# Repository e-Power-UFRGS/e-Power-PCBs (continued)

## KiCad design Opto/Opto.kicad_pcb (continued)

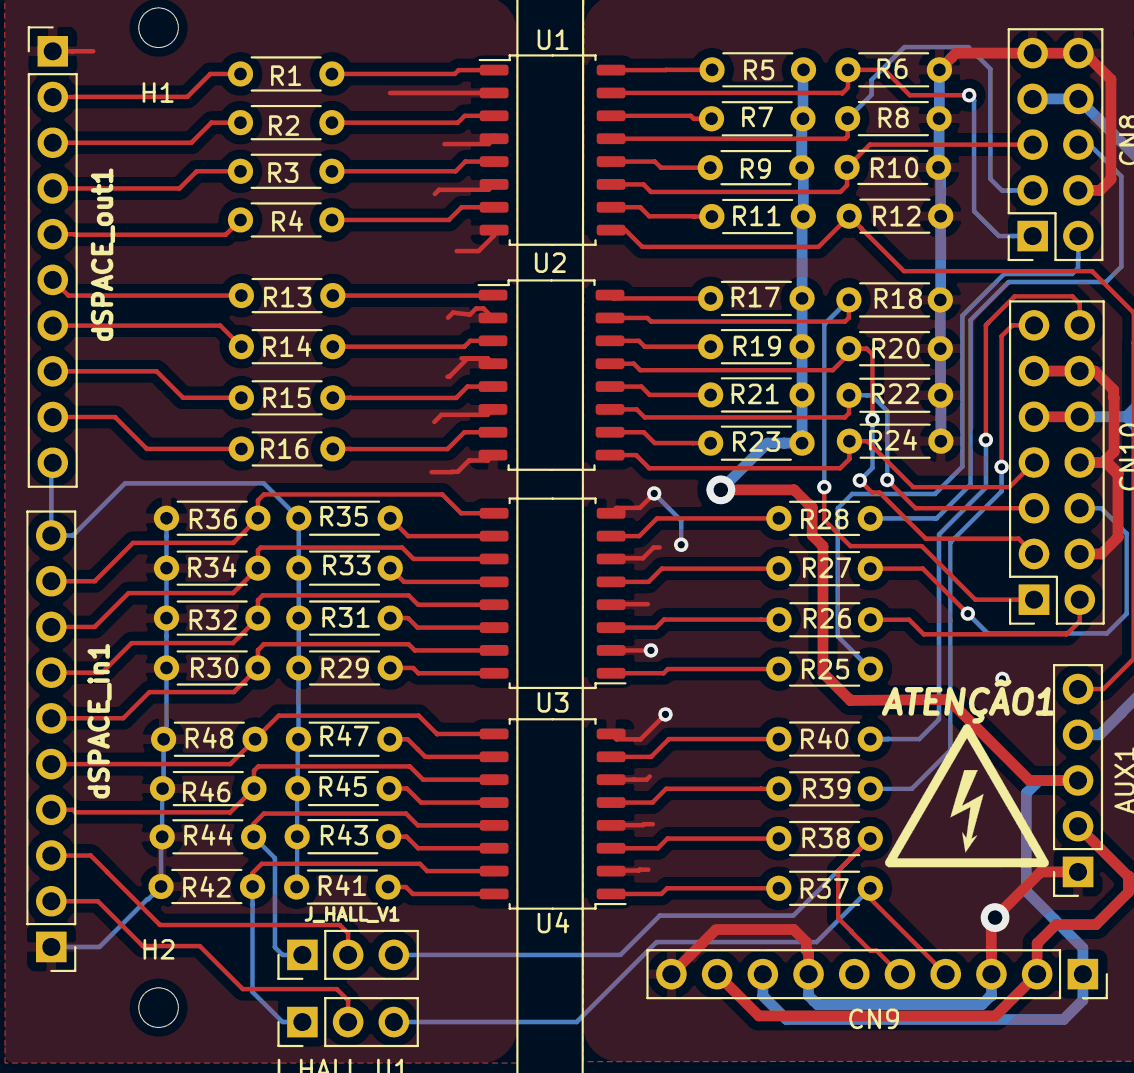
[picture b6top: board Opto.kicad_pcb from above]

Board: 2 copper layers, 65 parts (0 on the bottom side), 72 nets.

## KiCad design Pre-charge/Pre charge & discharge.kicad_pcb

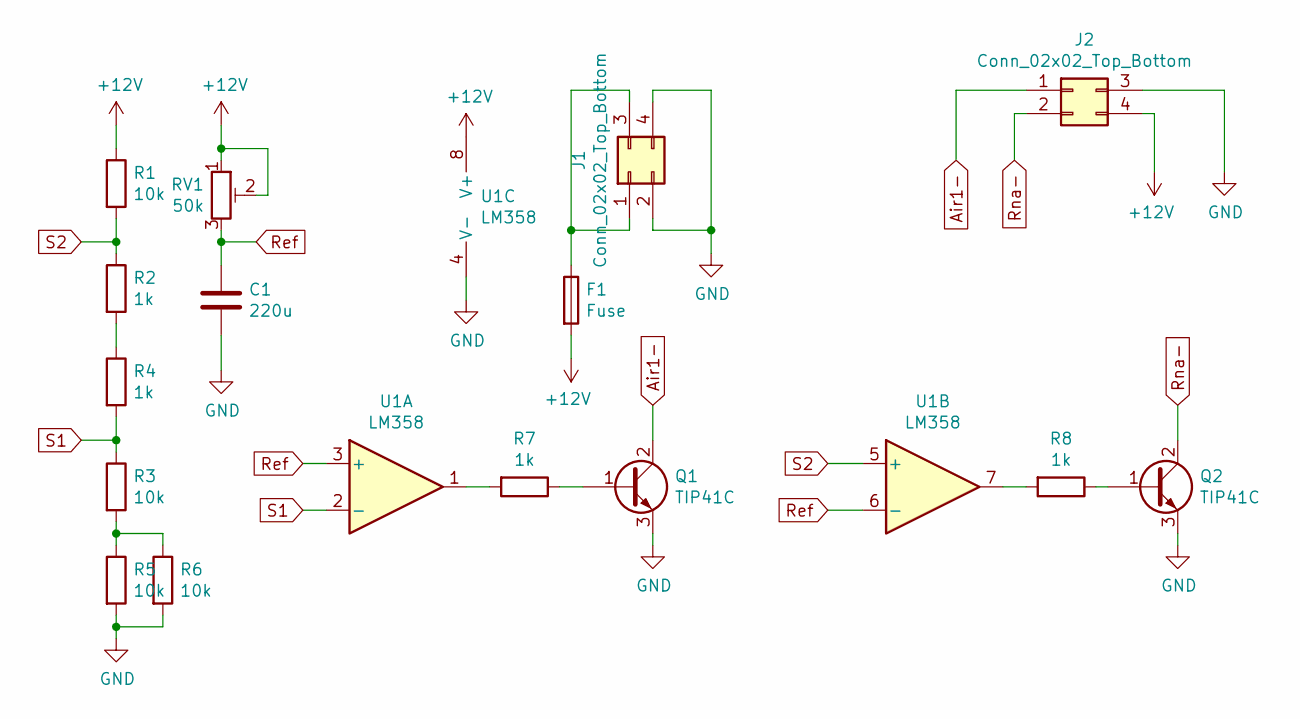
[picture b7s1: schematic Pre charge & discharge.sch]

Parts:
C1: 220u; CP_Elec_8x10
F1: Fuse; FUSE_1206_3216Metric
J1, J2: Conn_02x02_Top_Bottom; Molex_Mega-Fit_76825-0004_2x02_P5.70mm_Horizontal
Q1, Q2: TIP41C; TO-220-3_Vertical
R1, R3, R5, R6: 10k; R_0805_2012Metric
R2, R4, R7, R8: 1k; R_0805_2012Metric
RV1: 50k; Potentiometer_Bourns_3266Y_Vertical
U1: LM358; SOIC-8_3.9x4.9mm_P1.27mm

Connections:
+12V: F1.2, J2.4, R1.1, RV1.1, RV1.2, U1.8 (V+)
Air1-: J2.1, Q1.2 (C)
GND: C1.2, J1.2, J1.4, J2.3, Q1.3 (E), Q2.3 (E), R5.2, R6.2, U1.4 (V-)
unnamed: F1.1, J1.1, J1.3
unnamed: Q1.1 (B), R7.1
unnamed: Q2.1 (B), R8.1
unnamed: R2.2, R4.1
unnamed: R3.2, R5.1, R6.1
unnamed: R7.2, U1.1
unnamed: R8.2, U1.7
Ref: C1.1, RV1.3, U1.3 (+), U1.6 (-)
Rna-: J2.2, Q2.2 (C)
S1: R3.1, R4.2, U1.2 (-)
S2: R1.2, R2.1, U1.5 (+)

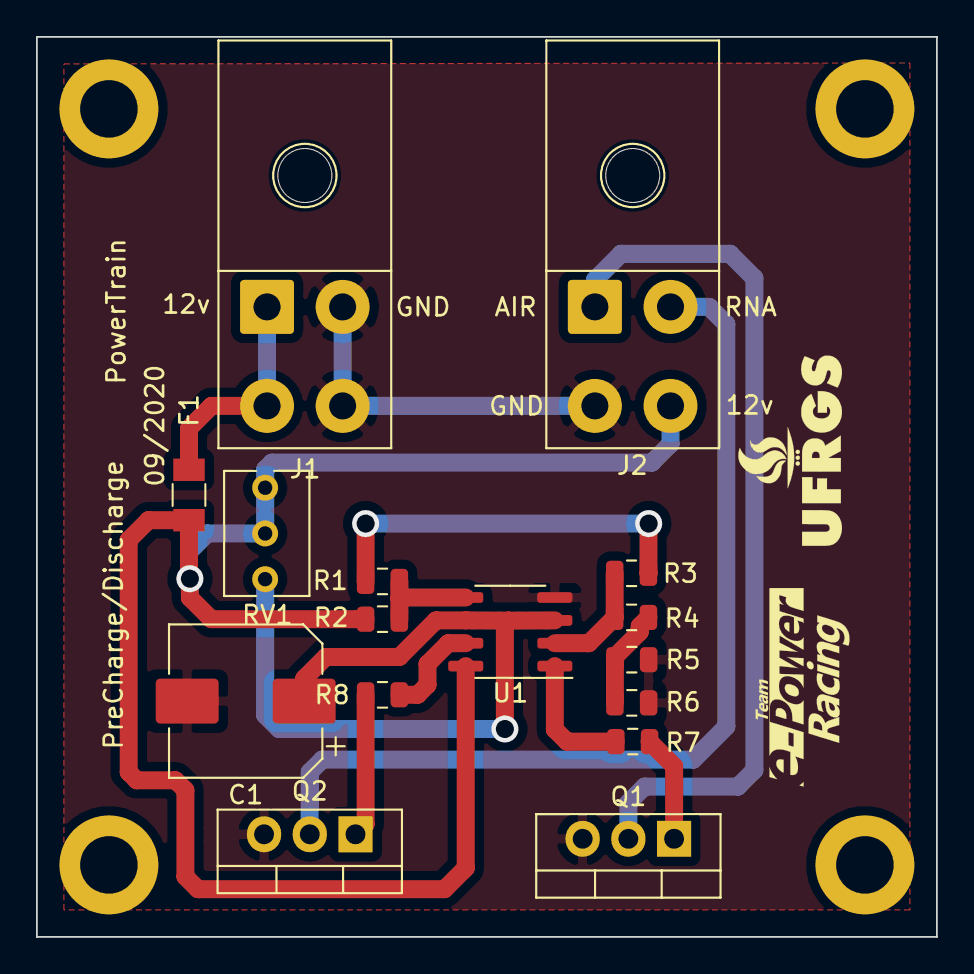
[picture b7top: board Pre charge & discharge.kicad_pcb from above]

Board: 2 copper layers, 50.0 x 50.0 mm, 16 parts (0 on the bottom side), 14 nets.
